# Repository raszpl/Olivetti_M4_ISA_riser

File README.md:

# Olivetti_M4_ISA_riser
Olivetti M4 ISA riser recreation to help with [Vogons: Olivetti riser board question](https://www.vogons.org/viewtopic.php?t=113104)  

## Resources
[Olivetti BA013](https://theretroweb.com/motherboards/s/olivetti-ba013-m300-02)  
dataino.it reverse engineered PCS11 Power connector [Vogons: Olivetti PCS33 (386 SX)/M-300 - Repairing](https://www.vogons.org/viewtopic.php?p=983836#p983836)  
RetroSpector78 'Olivetti M300-02 eBay "score" - kinda working (part 2)' https://www.youtube.com/watch?v=bMmtZ3Rd9ac  
TiBo's Retro Computers 'Olivetti PCS-44 80486sx - NOT again! It's almost like a recurring nightmare' https://www.youtube.com/watch?v=P1pw0pFJfUY  
Optionally [Olivetti M4-60/62/64/65/66](https://theretroweb.com/motherboards/s/olivetti-m4-60-62-64-65-66) but the riser doesnt seem 100% compatible, WTF was Olivetti smoking?

## Status

20%. Obvious tracks routes, some connections guessed. Needs a lot of verification work.

## Progress report

‎27/11/2026 forgot I proposed it :) spend ~2 hours laying out base template and connecting most obvious pins. [~20% there](https://raw.githubusercontent.com/raszpl/Olivetti_M4_ISA_riser/main/olivetti%20riser.png)  
15/11/2026 proposed

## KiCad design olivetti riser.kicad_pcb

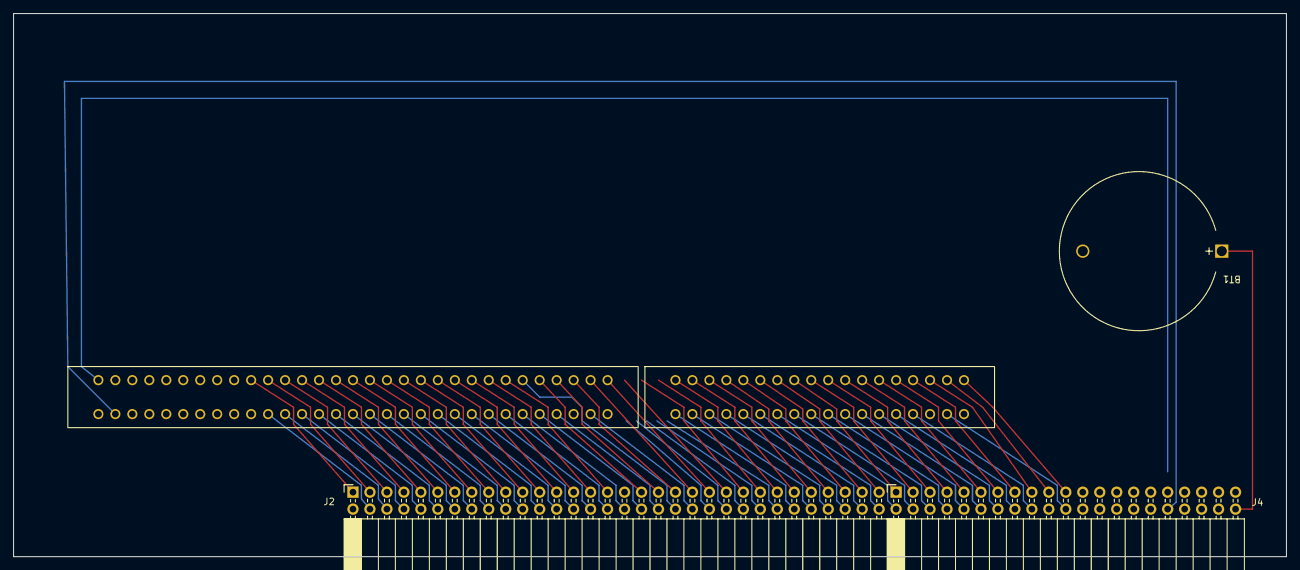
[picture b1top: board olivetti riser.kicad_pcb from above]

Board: 2 copper layers, 190.5 x 81.3 mm, 4 parts (0 on the bottom side), 82 nets.

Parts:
BT1: Battery; BatteryHolder_MYOUNG_BS-07-A1BJ001_CR2032
J1: Bus_ISA_16bit; ISA16
J2: Conn_02x31_Row_Letter_First; PinSocket_2x32_P2.54mm_Horizontal
J4: Conn_02x21_Row_Letter_First; PinSocket_2x21_P2.54mm_Horizontal

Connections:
+5V: J1.B3 (+5V), J1.B29 (+5V), J1.D16 (+5V), J4.29
+12V: J1.B9 (+12V), J4.23
-12V: J1.B7 (-12V), J4.25
/AEN: J1.A11 (AEN), J2.3
/CLK_14_318MHz: J1.B30 (OSC), J2.42
/CLK_ISA: J1.B20 (SYSCLK), J2.22
/DRQ0: J1.D9 (DRQ0), J4.6
/DRQ1: J1.B18 (DRQ1), J2.18
/DRQ2: J1.B6 (DRQ2), J4.28
/DRQ3: J1.B16 (DRQ3), J2.14
/DRQ5: J1.D11 (DRQ5), J4.10
/DRQ6: J1.D13 (DRQ6), J4.14
/DRQ7: J1.D15 (DRQ7), J4.18
/DT8: J1.C11 (SD8), J4.7
/DT9: J1.C12 (SD9), J4.9
/DT10: J1.C13 (SD10), J4.11
/DT11: J1.C14 (SD11), J4.13
/DT12: J1.C15 (SD12), J4.15
/DT13: J1.C16 (SD13), J4.17
/DT14: J1.C17 (SD14), J4.19
/DT15: J1.C18 (SD15), J4.21
/IRQ3: J1.B25 (IRQ3), J2.32
/IRQ4: J1.B24 (IRQ4), J2.30
/IRQ5: J1.B23 (IRQ5), J2.28
/IRQ6: J1.B22 (IRQ6), J2.26
/IRQ7: J1.B21 (IRQ7), J2.24
/IRQ10: J1.D3 (IRQ10), J2.58
/IRQ11: J1.D4 (IRQ11), J2.60
/IRQ12: J1.D5 (IRQ12), J2.62
/IRQ14: J1.D7 (IRQ14), J4.2
/IRQ15: J1.D6 (IRQ15), J2.64
/ISA_BALE: J1.B28 (BALE), J2.38
/ISA_IO_READY: J1.A10 (IOCHRDY), J2.1
/ISA_SBHE: J1.C1 (SBHE), J2.51
/LA17: J1.C8 (LA17), J4.1
/LA18: J1.C7 (LA18), J2.63
/LA19: J1.C6 (LA19), J2.61
/LA20: J1.C5 (LA20), J2.59
/LA21: J1.C4 (LA21), J2.57
/LA22: J1.C3 (LA22), J2.55
/LA23: J1.C2 (LA23), J2.53
/MASTER: J1.D17 (MASTER), J4.22
/RESET: J1.B2 (RESET), J4.34
/SA0: J1.A31 (SA0), J2.43
/SA1: J1.A30 (SA1), J2.41
/SA2: J1.A29 (SA2), J2.39
/SA3: J1.A28 (SA3), J2.37
/SA4: J1.A27 (SA4), J2.35
/SA5: J1.A26 (SA5), J2.40
/SA6: J1.A25 (SA6), J2.31
/SA7: J1.A24 (SA7), J2.29
/SA8: J1.A23 (SA8), J2.27
/SA9: J1.A22 (SA9), J2.25
/SA10: J1.A21 (SA10), J2.23
/SA11: J1.A20 (SA11), J2.21
/SA12: J1.A19 (SA12), J2.19
/SA13: J1.A18 (SA13), J2.17
/SA14: J1.A17 (SA14), J2.15
/SA15: J1.A16 (SA15), J2.13
/SA16: J1.A15 (SA16), J2.11
/SA17: J1.A14 (SA17), J2.9
/SA18: J1.A13 (SA18), J2.7
/SA19: J1.A12 (SA19), J2.5
/TC: J1.B27 (TC), J2.36
/~DACK0: J1.D8 (~DACK0), J4.4
/~DACK1: J1.B17 (~DACK1), J2.16
/~DACK2: J1.B26 (~DACK2), J2.34
/~DACK3: J1.B15 (~DACK3), J2.12
/~DACK5: J1.D10 (~DACK5), J4.8
/~DACK6: J1.D12 (~DACK6), J4.12
/~DACK7: J1.D14 (~DACK7), J4.16
/~IO_RD: J1.B14 (~IOR), J2.10
/~IO_WR: J1.B13 (~IOW), J2.8
/~ISA_IOCS16: J1.D2 (~IOCS16), J2.56
/~ISA_MEMCS16: J1.D1 (~MEMCS16), J2.54
/~ISA_MEM_RD: J1.B12 (~SMEMR), J2.6
/~ISA_MEM_WR: J1.B11 (~SMEMW), J2.4
/~MEMR: J1.C9 (~MEMR), J4.3
/~MEMW: J1.C10 (~MEMW), J4.5
/~REFRESH: J1.B19 (~REFRESH), J2.20
GND: BT1.2 (-), J1.B1 (GND), J1.B10 (GND), J1.B31 (GND), J1.D18 (GND), J4.33, J4.35, J4.37
unnamed: BT1.1 (+), J4.42
